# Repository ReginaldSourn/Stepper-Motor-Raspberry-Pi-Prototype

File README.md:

# raspberry_motor
for controlling motor

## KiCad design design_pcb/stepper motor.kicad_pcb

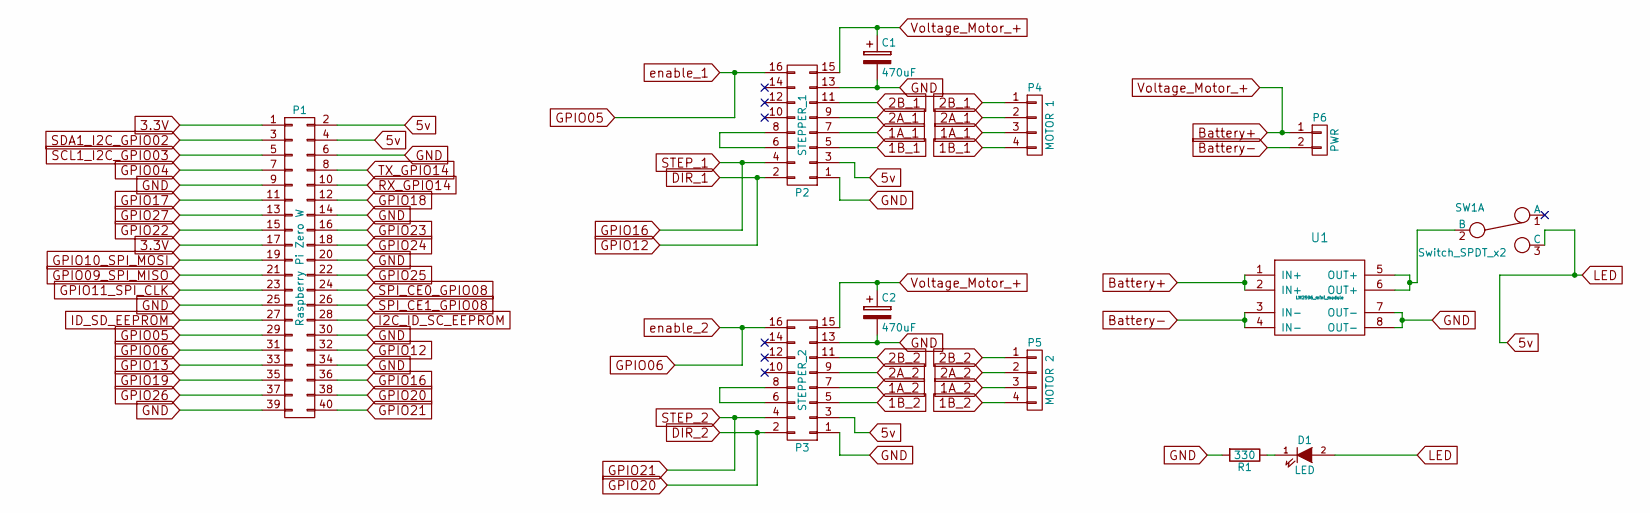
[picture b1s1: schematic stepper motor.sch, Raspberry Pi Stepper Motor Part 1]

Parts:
C1, C2: 470uF; C_Radial_D7.5_L11.2_P2.5
D1: LED; LED_0805
P1: Raspberry Pi Zero W; Socket_Strip_Straight_2x20
P2: STEPPER_1; A4988_Stepper_Motor_Driver
P3: STEPPER_2; A4988_Stepper_Motor_Driver
P4: MOTOR 1; Pin_Header_Straight_1x04
P5: MOTOR 2; Pin_Header_Straight_1x04
P6: PWR; Socket_Strip_Straight_1x02
R1: 330; R_0805_HandSoldering
SW1: Switch_SPDT_x2; SW_SPDT
U1: LM2596_mini_module; LM2596

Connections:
1A_1: P2.7, P4.3
1A_2: P3.7, P5.3
1B_1: P2.5, P4.4
1B_2: P3.5, P5.4
2A_1: P2.9, P4.2
2A_2: P3.9, P5.2
2B_1: P2.11, P4.1
2B_2: P3.11, P5.1
3.3V: P1.1, P1.17
5v: D1.2 (A), P1.2, P1.4, P2.3, P3.3, SW1.3 (C)
Battery+: C1.1, C2.1, P2.15, P3.15, P6.1, U1.1 (IN+), U1.2 (IN+)
Battery-: P6.2, U1.3 (IN-), U1.4 (IN-)
DIR_1: P1.32, P2.2
DIR_2: P1.38, P3.2
GND: C1.2, C2.2, P1.6, P1.9, P1.14, P1.20, P1.25, P1.30, P1.34, P1.39, P2.1, P2.13, P3.1, P3.13, R1.2, U1.7 (OUT-), U1.8 (OUT-)
GPIO04: P1.7
GPIO05: P1.29, P2.16
GPIO06: P1.31, P3.16
GPIO09_SPI_MISO: P1.21
GPIO10_SPI_MOSI: P1.19
GPIO11_SPI_CLK: P1.23
GPIO13: P1.33
GPIO16: P1.36, P2.4
GPIO17: P1.11
GPIO18: P1.12
GPIO19: P1.35
GPIO21: P1.40, P3.4
GPIO22: P1.15
GPIO23: P1.16
GPIO24: P1.18
GPIO25: P1.22
GPIO26: P1.37
GPIO27: P1.13
I2C_ID_SC_EEPROM: P1.28
ID_SD_EEPROM: P1.27
unnamed: D1.1 (K), R1.1
unnamed: P2.6, P2.8
unnamed: P3.6, P3.8
unnamed: SW1.2 (B), U1.5 (OUT+), U1.6 (OUT+)
RX_GPIO14: P1.10
SCL1_I2C_GPIO03: P1.5
SDA1_I2C_GPIO02: P1.3
SPI_CE0_GPIO08: P1.24
SPI_CE1_GPIO08: P1.26
TX_GPIO14: P1.8

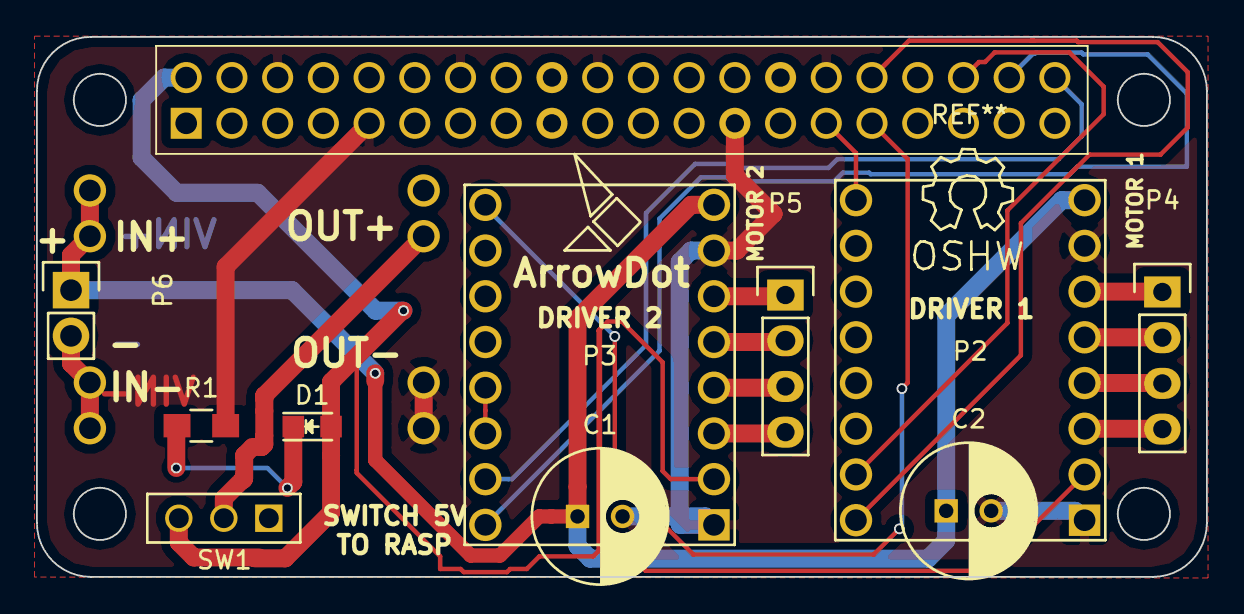
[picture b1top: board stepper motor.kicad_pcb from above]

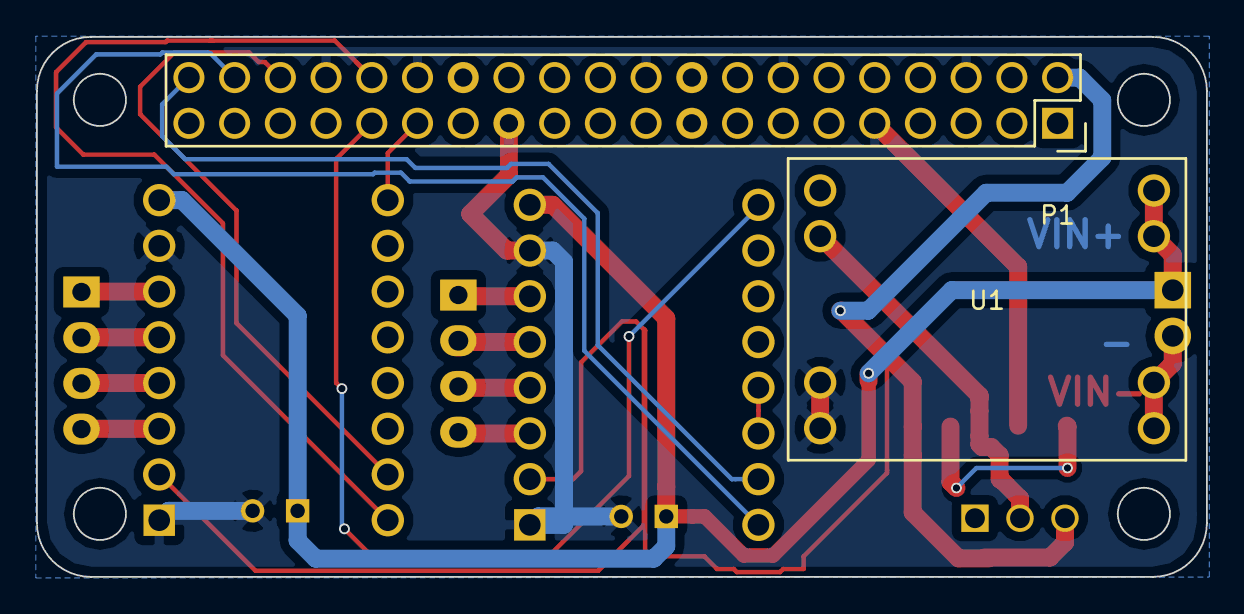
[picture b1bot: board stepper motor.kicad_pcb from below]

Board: 2 copper layers, 65.0 x 30.0 mm, 12 parts (2 on the bottom side), 23 nets.
